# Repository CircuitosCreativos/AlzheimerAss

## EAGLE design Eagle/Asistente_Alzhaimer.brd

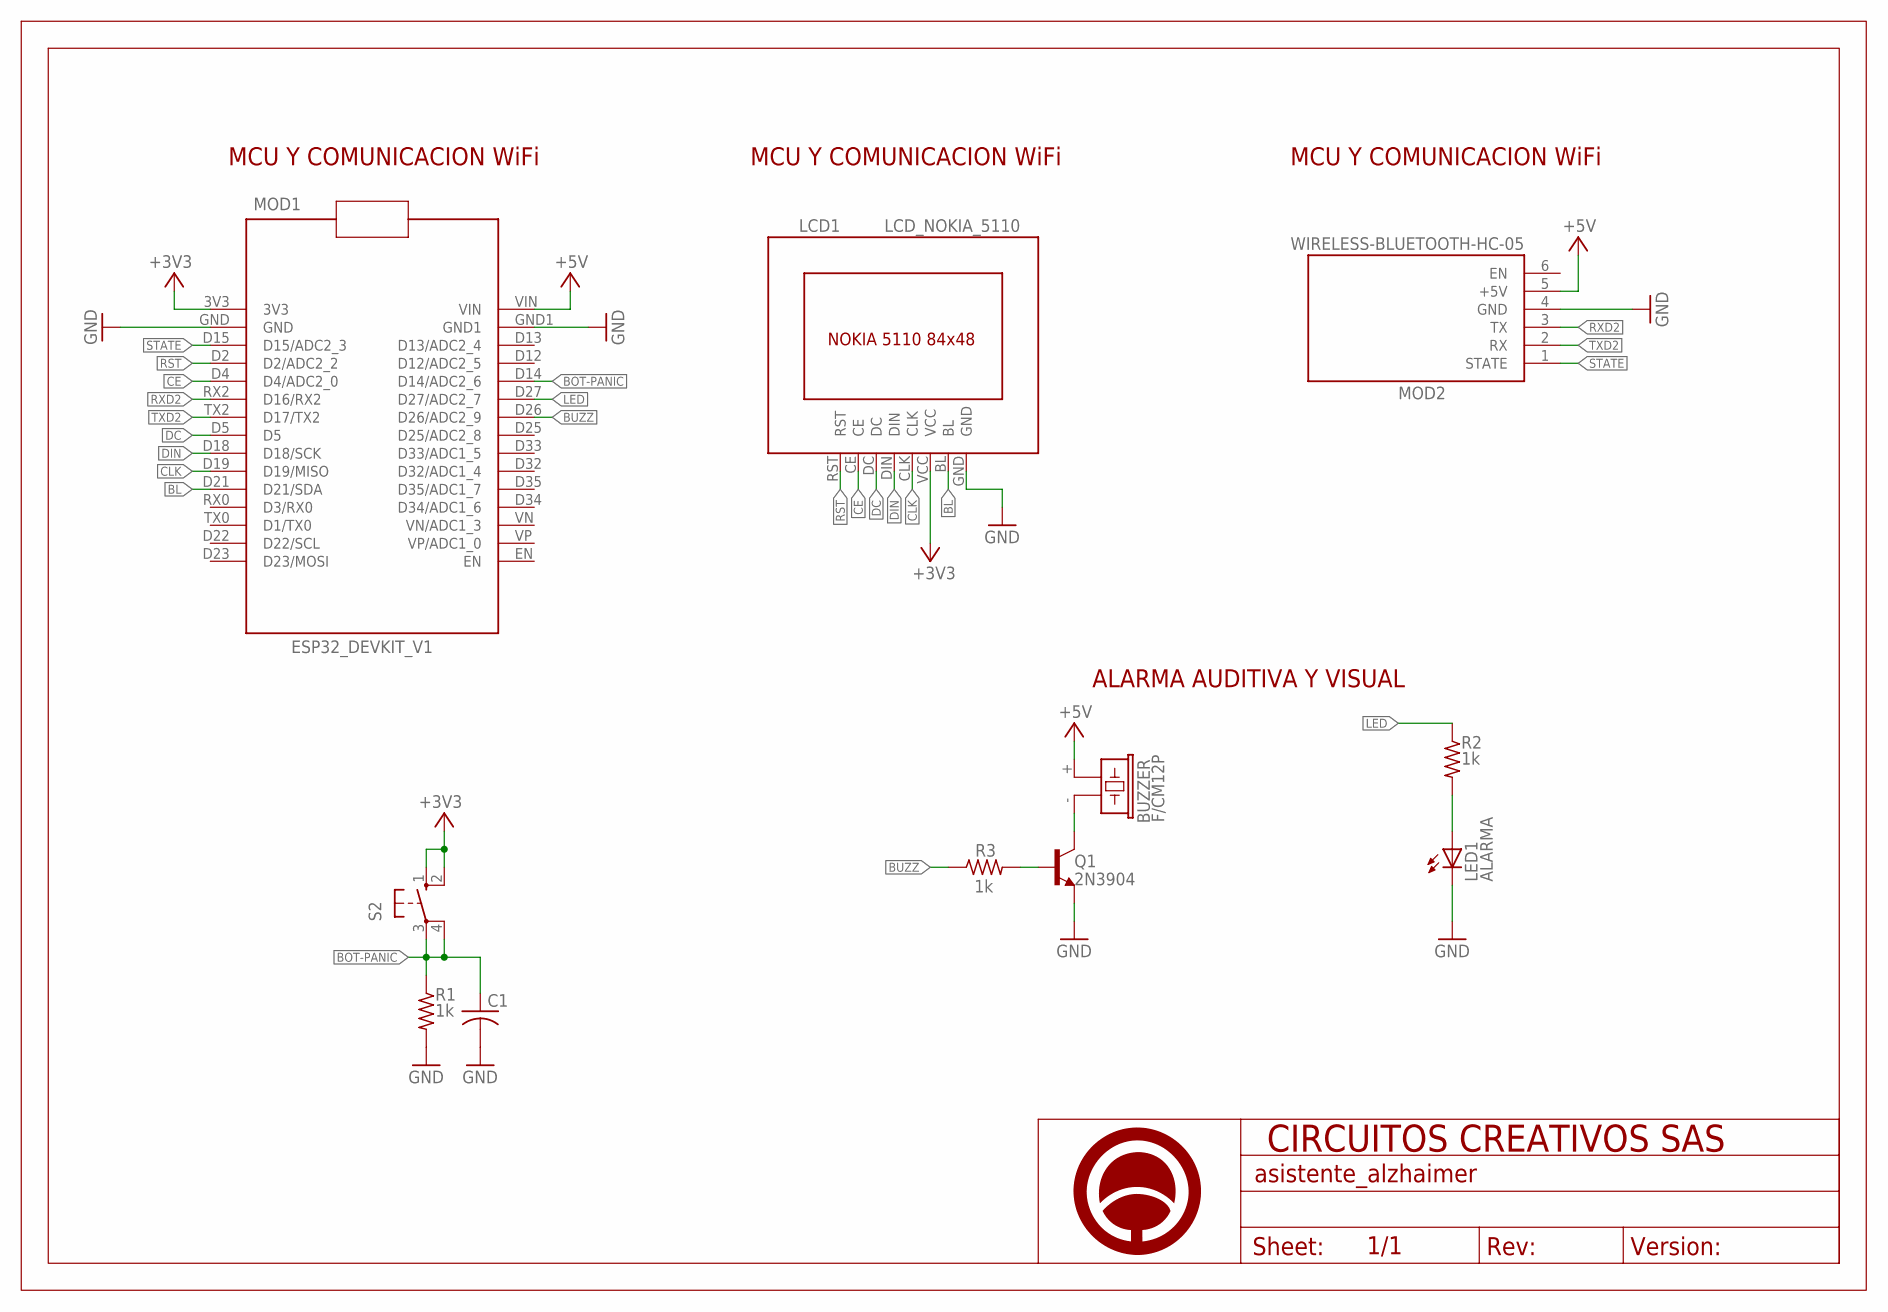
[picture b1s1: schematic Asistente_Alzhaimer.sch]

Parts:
BUZZER: F/CM12P
C1: C-US050-025X075; C050-025X075
LCD1: LCD_NOKIA_5110; NOKIA_5110_THT
LED1: ALARMA; LED3MM
MOD1: ESP32_DEVKIT_V1
MOD2: WIRELESS-BLUETOOTH-HC-05
Q1: 2N3904; TO-92
R1, R2, R3: 1k; 0204/7
S2: 10-XX; B3F-10XX
U$1: A4_HORIZONTAL; LOGO

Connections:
+3V3: LCD1.VCC, MOD1.3V3, S2.1 (S), S2.2 (S1)
+5V: BUZZER.+ (1), MOD1.VIN, MOD2.5 (+5V)
BL: LCD1.BL, MOD1.D21 (D21/SDA)
BOT-PANIC: C1.1, MOD1.D14 (D14/ADC2_6), R1.1, S2.3, S2.4 (P1)
BUZZ: MOD1.D26 (D26/ADC2_9), R3.1
CE: LCD1.CE, MOD1.D4 (D4/ADC2_0)
CLK: LCD1.CLK, MOD1.D19 (D19/MISO)
DC: LCD1.DC, MOD1.D5
DIN: LCD1.DIN, MOD1.D18 (D18/SCK)
GND: C1.2, LCD1.GND, LED1.K (C), MOD1.GND, MOD1.GND1, MOD2.4 (GND), Q1.1 (E), R1.2
LED: MOD1.D27 (D27/ADC2_7), R2.1
unnamed: LED1.A, R2.2
unnamed: Q1.2 (B), R3.2
unnamed: BUZZER.- (2), Q1.3 (C)
RST: LCD1.RST, MOD1.D2 (D2/ADC2_2)
RXD2: MOD1.RX2 (D16/RX2), MOD2.3 (TX)
STATE: MOD1.D15 (D15/ADC2_3), MOD2.1 (STATE)
TXD2: MOD1.TX2 (D17/TX2), MOD2.2 (RX)

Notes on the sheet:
ALARMA AUDITIVA Y VISUAL
MCU Y COMUNICACION WiFi

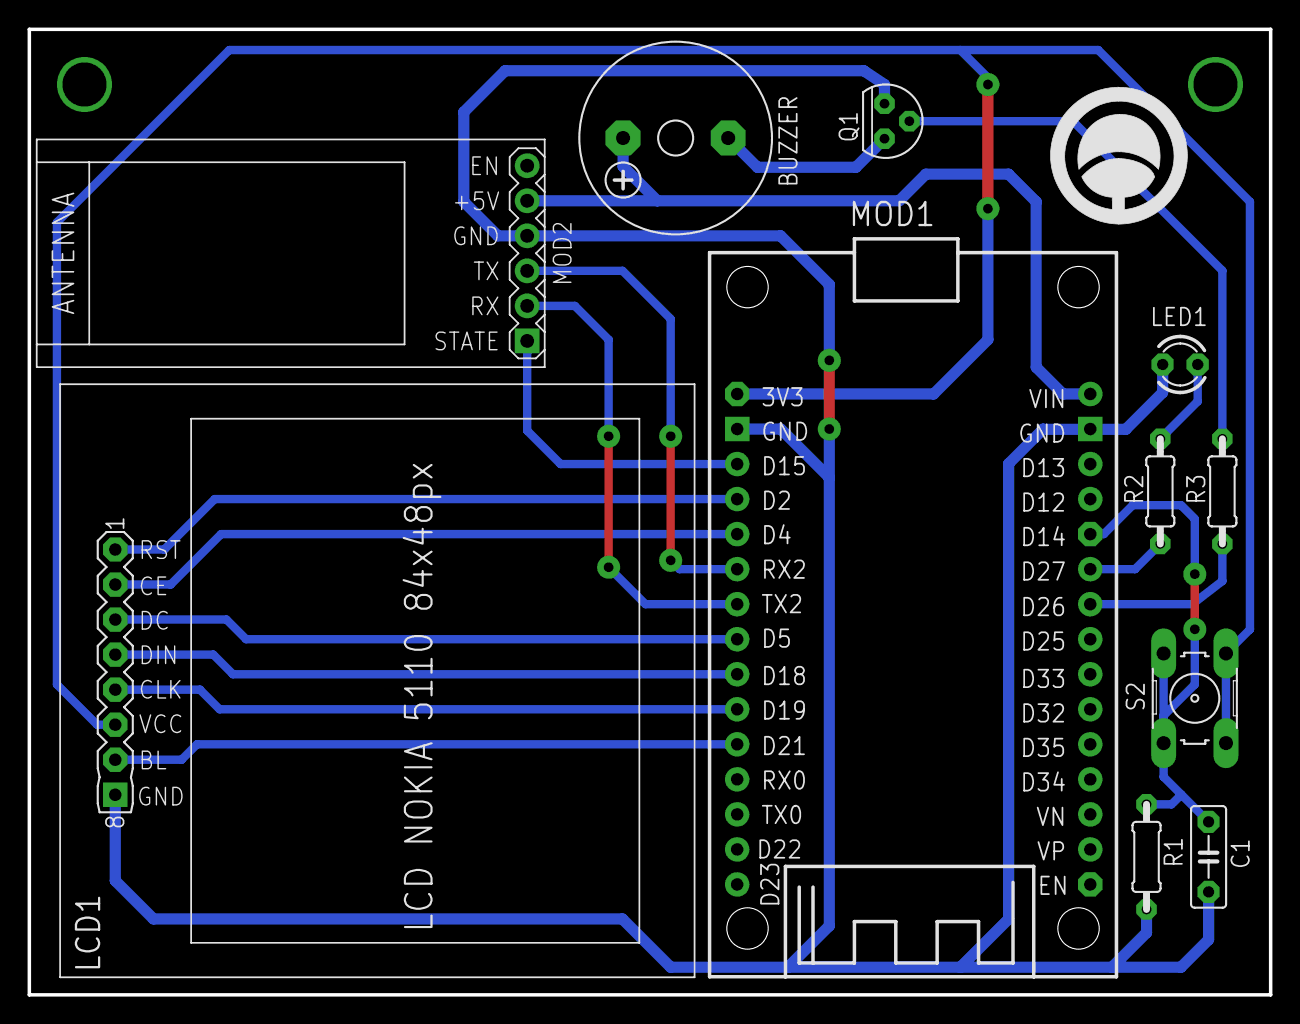
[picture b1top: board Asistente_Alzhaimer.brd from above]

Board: 2 copper layers, 90.0 x 70.0 mm, 12 parts (0 on the bottom side), 18 nets.

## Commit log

2019-05-10 Commit inicial, cambiar MKR1000 por ESP32
2019-05-10 Primeros pasos LCD Nokia 5110
2019-05-10 Completado comunicacion basica con blynk ESP32
2019-05-11 Conexion exitosa con sensor Hub nano
2019-05-11 Add lcd mensaje conexion exitosa y error
2019-05-11 Completado comunicacion basica con todo el Hardware
2019-05-14 Add funcion confirmarCaida
2019-05-14 Creado Alarmas.ino
2019-05-14 Add menuAlarmas para control de estados
2019-05-14 Add mfuncion setBlynkWidgets
2019-05-14 Add alarma por temperatura
2019-05-14 Revert "Add alarma por temperatura"
    This reverts commit 0443742994e362710b3b0a837980e471c1c06687.
2019-05-14 Add EVENTOR hacer ejercicio
2019-05-14 Add EVENTOR medicamento y sanitario
2019-05-15 SCH con ESP32 al 50%
2019-06-05 Terminado SCH y BRD

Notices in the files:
parts and their libraries:
diy-modules: Released under the Creative Commons Attribution 4.0 International License: http://creativecommons.org/licenses/by/4.0
